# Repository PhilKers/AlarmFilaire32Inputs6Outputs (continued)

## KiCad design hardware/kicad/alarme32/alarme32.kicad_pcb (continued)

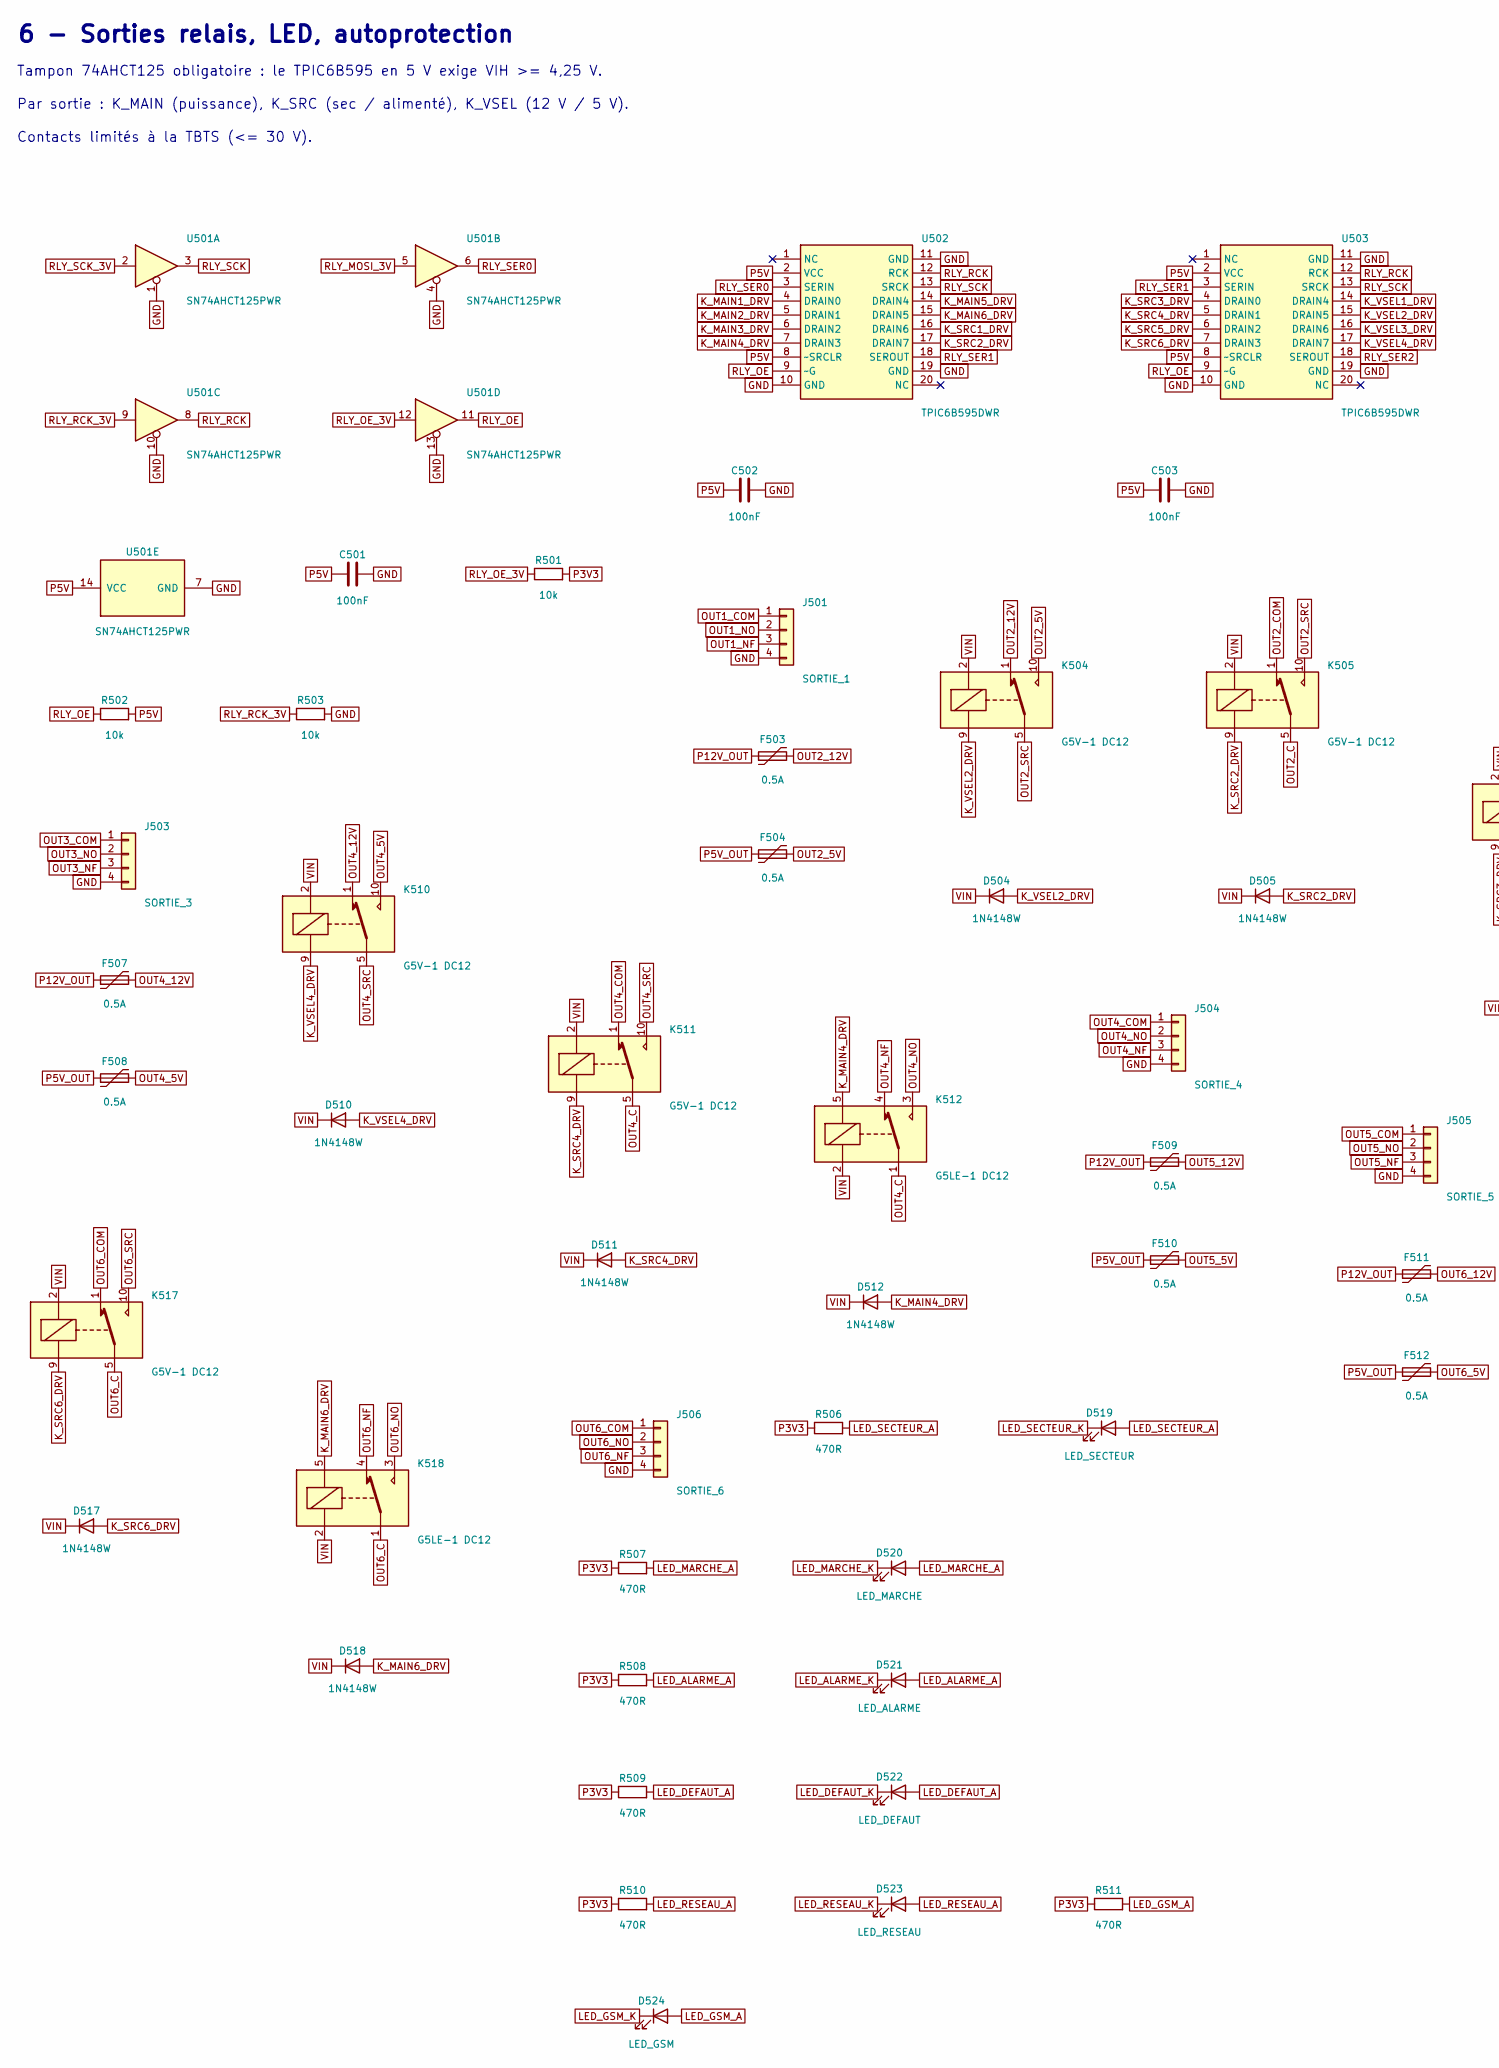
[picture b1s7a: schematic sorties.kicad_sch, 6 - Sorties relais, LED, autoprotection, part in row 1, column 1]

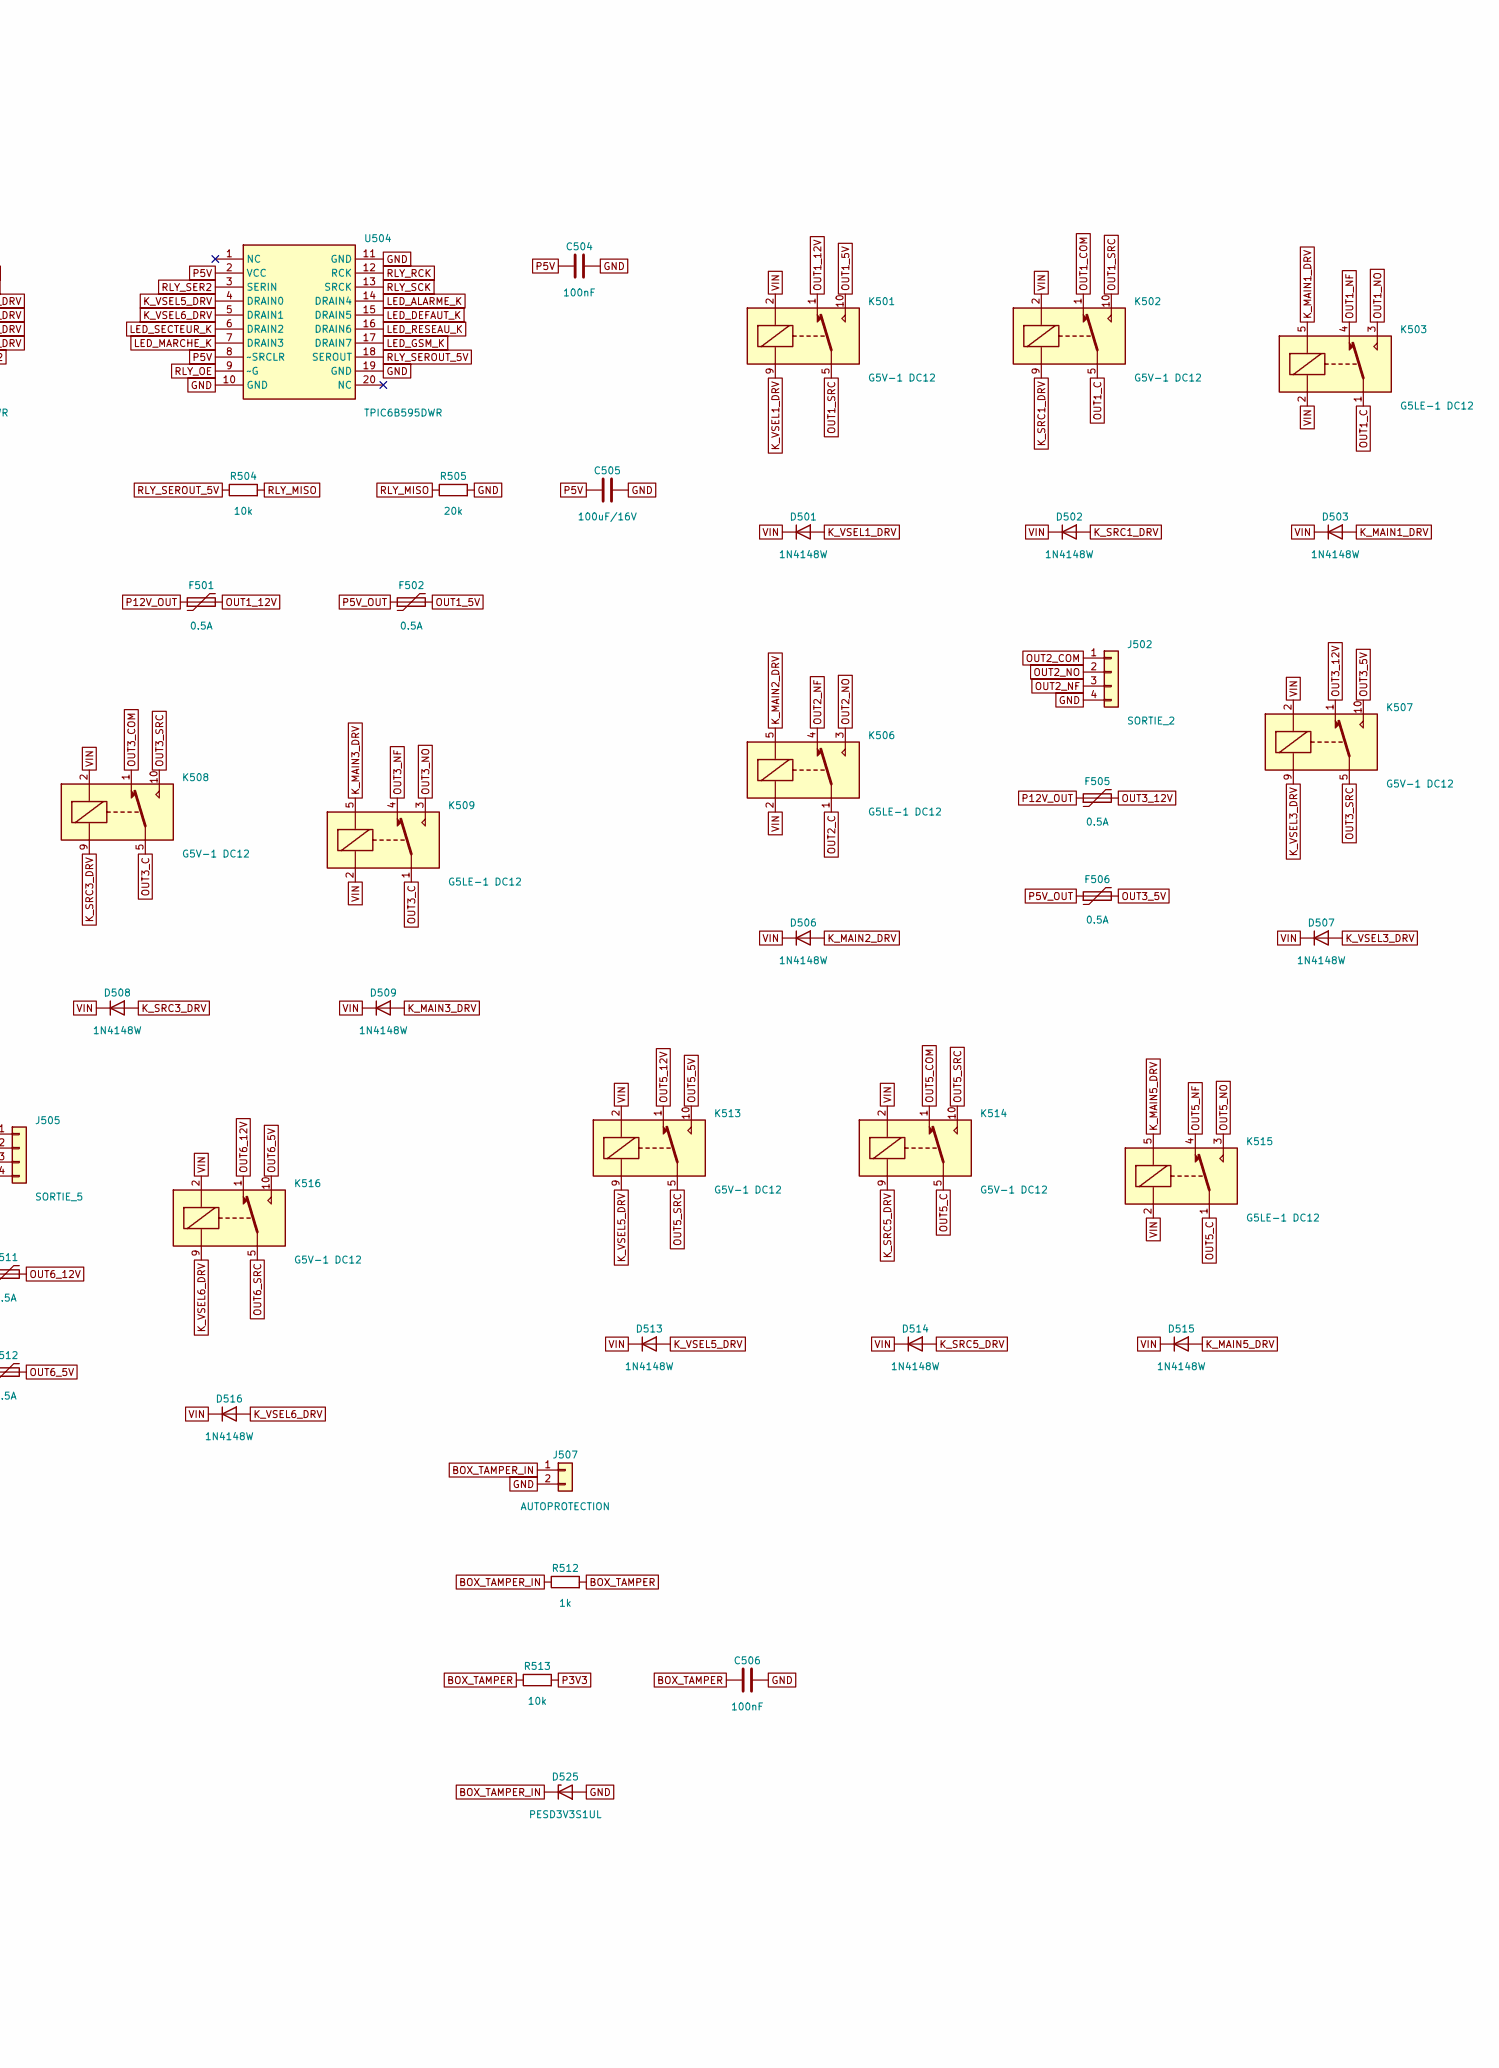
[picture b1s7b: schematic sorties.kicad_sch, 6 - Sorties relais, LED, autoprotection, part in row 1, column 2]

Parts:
C501, C502, C503, C504, C506: 100nF; C_0603_1608Metric
C505: 100uF/16V; C_1210_3225Metric
D501, D502, D503, D504, D505, D506, D507, D508, D509, D510, D511, D512, D513, D514, D515, D516, D517, D518: 1N4148W; D_SOD-123
D519: LED_SECTEUR; LED_D3.0mm
D520: LED_MARCHE; LED_D3.0mm
D521: LED_ALARME; LED_D3.0mm
D522: LED_DEFAUT; LED_D3.0mm
D523: LED_RESEAU; LED_D3.0mm
D524: LED_GSM; LED_D3.0mm
D525: PESD3V3S1UL; D_SOD-323
F501, F502, F503, F504, F505, F506, F507, F508, F509, F510, F511, F512: 0.5A; Fuse_1206_3216Metric
J501: SORTIE_1; TerminalBlock_Phoenix_MKDS-1,5-4-5.08_1x04_P5.08mm_Horizont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
J502: SORTIE_2; TerminalBlock_Phoenix_MKDS-1,5-4-5.08_1x04_P5.08mm_Horizont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
J503: SORTIE_3; TerminalBlock_Phoenix_MKDS-1,5-4-5.08_1x04_P5.08mm_Horizont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
J504: SORTIE_4; TerminalBlock_Phoenix_MKDS-1,5-4-5.08_1x04_P5.08mm_Horizont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
J505: SORTIE_5; TerminalBlock_Phoenix_MKDS-1,5-4-5.08_1x04_P5.08mm_Horizont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
J506: SORTIE_6; TerminalBlock_Phoenix_MKDS-1,5-4-5.08_1x04_P5.08mm_Horizont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
J507: AUTOPROTECTION; PinHeader_1x02_P2.54mm_Vertical
K501, K502, K504, K505, K507, K508, K510, K511, K513, K514, K516, K517: G5V-1 DC12; Relay_SPDT_Omron_G5V-1
K503, K506, K509, K512, K515, K518: G5LE-1 DC12; Relay_SPDT_Omron-G5LE-1
R501, R502, R503, R504, R513: 10k; R_0603_1608Metric
R505: 20k; R_0603_1608Metric
R506, R507, R508, R509, R510, R511: 470R; R_0603_1608Metric
R512: 1k; R_0603_1608Metric
U501: SN74AHCT125PWR; TSSOP-14_4.4x5mm_P0.65mm
U502, U503, U504: TPIC6B595DWR; SOIC-20W_7.5x12.8mm_P1.27mm

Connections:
BOX_TAMPER: C506.1, R512.2, R513.1; also elsewhere on the board
BOX_TAMPER_IN: D525.1 (K), J507.1, R512.1
GND: C501.2, C502.2, C503.2, C504.2, C505.2, C506.2, D525.2 (A), J501.4, J502.4, J503.4, J504.4, J505.4, J506.4, J507.2, R503.2, R505.2, U501.1, U501.4, U501.7 (GND), U501.10, U501.13, U502.10 (GND), U502.11 (GND), U502.19 (GND), U503.10 (GND), U503.11 (GND), U503.19 (GND), U504.10 (GND), U504.11 (GND), U504.19 (GND); also elsewhere on the board
K_MAIN1_DRV: D503.2 (A), K503.5, U502.4 (DRAIN0)
K_MAIN2_DRV: D506.2 (A), K506.5, U502.5 (DRAIN1)
K_MAIN3_DRV: D509.2 (A), K509.5, U502.6 (DRAIN2)
K_MAIN4_DRV: D512.2 (A), K512.5, U502.7 (DRAIN3)
K_MAIN5_DRV: D515.2 (A), K515.5, U502.14 (DRAIN4)
K_MAIN6_DRV: D518.2 (A), K518.5, U502.15 (DRAIN5)
K_SRC1_DRV: D502.2 (A), K502.9, U502.16 (DRAIN6)
K_SRC2_DRV: D505.2 (A), K505.9, U502.17 (DRAIN7)
K_SRC3_DRV: D508.2 (A), K508.9, U503.4 (DRAIN0)
K_SRC4_DRV: D511.2 (A), K511.9, U503.5 (DRAIN1)
K_SRC5_DRV: D514.2 (A), K514.9, U503.6 (DRAIN2)
K_SRC6_DRV: D517.2 (A), K517.9, U503.7 (DRAIN3)
K_VSEL1_DRV: D501.2 (A), K501.9, U503.14 (DRAIN4)
K_VSEL2_DRV: D504.2 (A), K504.9, U503.15 (DRAIN5)
K_VSEL3_DRV: D507.2 (A), K507.9, U503.16 (DRAIN6)
K_VSEL4_DRV: D510.2 (A), K510.9, U503.17 (DRAIN7)
K_VSEL5_DRV: D513.2 (A), K513.9, U504.4 (DRAIN0)
K_VSEL6_DRV: D516.2 (A), K516.9, U504.5 (DRAIN1)
LED_ALARME_A: D521.2 (A), R508.2
LED_ALARME_K: D521.1 (K), U504.14 (DRAIN4)
LED_DEFAUT_A: D522.2 (A), R509.2
LED_DEFAUT_K: D522.1 (K), U504.15 (DRAIN5)
LED_GSM_A: D524.2 (A), R511.2
LED_GSM_K: D524.1 (K), U504.17 (DRAIN7)
LED_MARCHE_A: D520.2 (A), R507.2
LED_MARCHE_K: D520.1 (K), U504.7 (DRAIN3)
LED_RESEAU_A: D523.2 (A), R510.2
LED_RESEAU_K: D523.1 (K), U504.16 (DRAIN6)
LED_SECTEUR_A: D519.2 (A), R506.2
LED_SECTEUR_K: D519.1 (K), U504.6 (DRAIN2)
OUT1_5V: F502.2, K501.10
OUT1_12V: F501.2, K501.1
OUT1_C: K502.5, K502.6, K503.1
OUT1_COM: J501.1, K502.1
OUT1_NF: J501.3, K503.4
OUT1_NO: J501.2, K503.3
OUT1_SRC: K501.5, K501.6, K502.10
OUT2_5V: F504.2, K504.10
OUT2_12V: F503.2, K504.1
OUT2_C: K505.5, K505.6, K506.1
OUT2_COM: J502.1, K505.1
OUT2_NF: J502.3, K506.4
OUT2_NO: J502.2, K506.3
OUT2_SRC: K504.5, K504.6, K505.10
OUT3_5V: F506.2, K507.10
OUT3_12V: F505.2, K507.1
OUT3_C: K508.5, K508.6, K509.1
OUT3_COM: J503.1, K508.1
OUT3_NF: J503.3, K509.4
OUT3_NO: J503.2, K509.3
OUT3_SRC: K507.5, K507.6, K508.10
OUT4_5V: F508.2, K510.10
OUT4_12V: F507.2, K510.1
OUT4_C: K511.5, K511.6, K512.1
OUT4_COM: J504.1, K511.1
OUT4_NF: J504.3, K512.4
OUT4_NO: J504.2, K512.3
OUT4_SRC: K510.5, K510.6, K511.10
OUT5_5V: F510.2, K513.10
OUT5_12V: F509.2, K513.1
OUT5_C: K514.5, K514.6, K515.1
OUT5_COM: J505.1, K514.1
OUT5_NF: J505.3, K515.4
OUT5_NO: J505.2, K515.3
OUT5_SRC: K513.5, K513.6, K514.10
OUT6_5V: F512.2, K516.10
OUT6_12V: F511.2, K516.1
OUT6_C: K517.5, K517.6, K518.1
OUT6_COM: J506.1, K517.1
OUT6_NF: J506.3, K518.4
OUT6_NO: J506.2, K518.3
OUT6_SRC: K516.5, K516.6, K517.10
P3V3: R501.2, R506.1, R507.1, R508.1, R509.1, R510.1, R511.1, R513.2; also elsewhere on the board
P5V: C501.1, C502.1, C503.1, C504.1, C505.1, R502.2, U501.14 (VCC), U502.2 (VCC), U502.8 (~SRCLR), U503.2 (VCC), U503.8 (~SRCLR), U504.2 (VCC), U504.8 (~SRCLR); also elsewhere on the board
P5V_OUT: F502.1, F504.1, F506.1, F508.1, F510.1, F512.1; also elsewhere on the board
P12V_OUT: F501.1, F503.1, F505.1, F507.1, F509.1, F511.1; also elsewhere on the board
RLY_MISO: R504.2, R505.1; also elsewhere on the board
RLY_MOSI_3V: U501.5; also elsewhere on the board
RLY_OE: R502.1, U501.11, U502.9 (~G), U503.9 (~G), U504.9 (~G)
RLY_OE_3V: R501.1, U501.12; also elsewhere on the board
RLY_RCK: U501.8, U502.12 (RCK), U503.12 (RCK), U504.12 (RCK)
RLY_RCK_3V: R503.1, U501.9; also elsewhere on the board
RLY_SCK: U501.3, U502.13 (SRCK), U503.13 (SRCK), U504.13 (SRCK)
RLY_SCK_3V: U501.2; also elsewhere on the board
RLY_SER0: U501.6, U502.3 (SERIN)
RLY_SER1: U502.18 (SEROUT), U503.3 (SERIN)
RLY_SER2: U503.18 (SEROUT), U504.3 (SERIN)
RLY_SEROUT_5V: R504.1, U504.18 (SEROUT)
VIN: D501.1 (K), D502.1 (K), D503.1 (K), D504.1 (K), D505.1 (K), D506.1 (K), D507.1 (K), D508.1 (K), D509.1 (K), D510.1 (K), D511.1 (K), D512.1 (K), D513.1 (K), D514.1 (K), D515.1 (K), D516.1 (K), D517.1 (K), D518.1 (K), K501.2, K502.2, K503.2, K504.2, K505.2, K506.2, K507.2, K508.2, K509.2, K510.2, K511.2, K512.2, K513.2, K514.2, K515.2, K516.2, K517.2, K518.2; also elsewhere on the board

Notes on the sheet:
6 - Sorties relais, LED, autoprotection
Tampon 74AHCT125 obligatoire : le TPIC6B595 en 5 V exige VIH >= 4,25 V.
Par sortie : K_MAIN (puissance), K_SRC (sec / alimenté), K_VSEL (12 V / 5 V).
Contacts limités à la TBTS (<= 30 V).

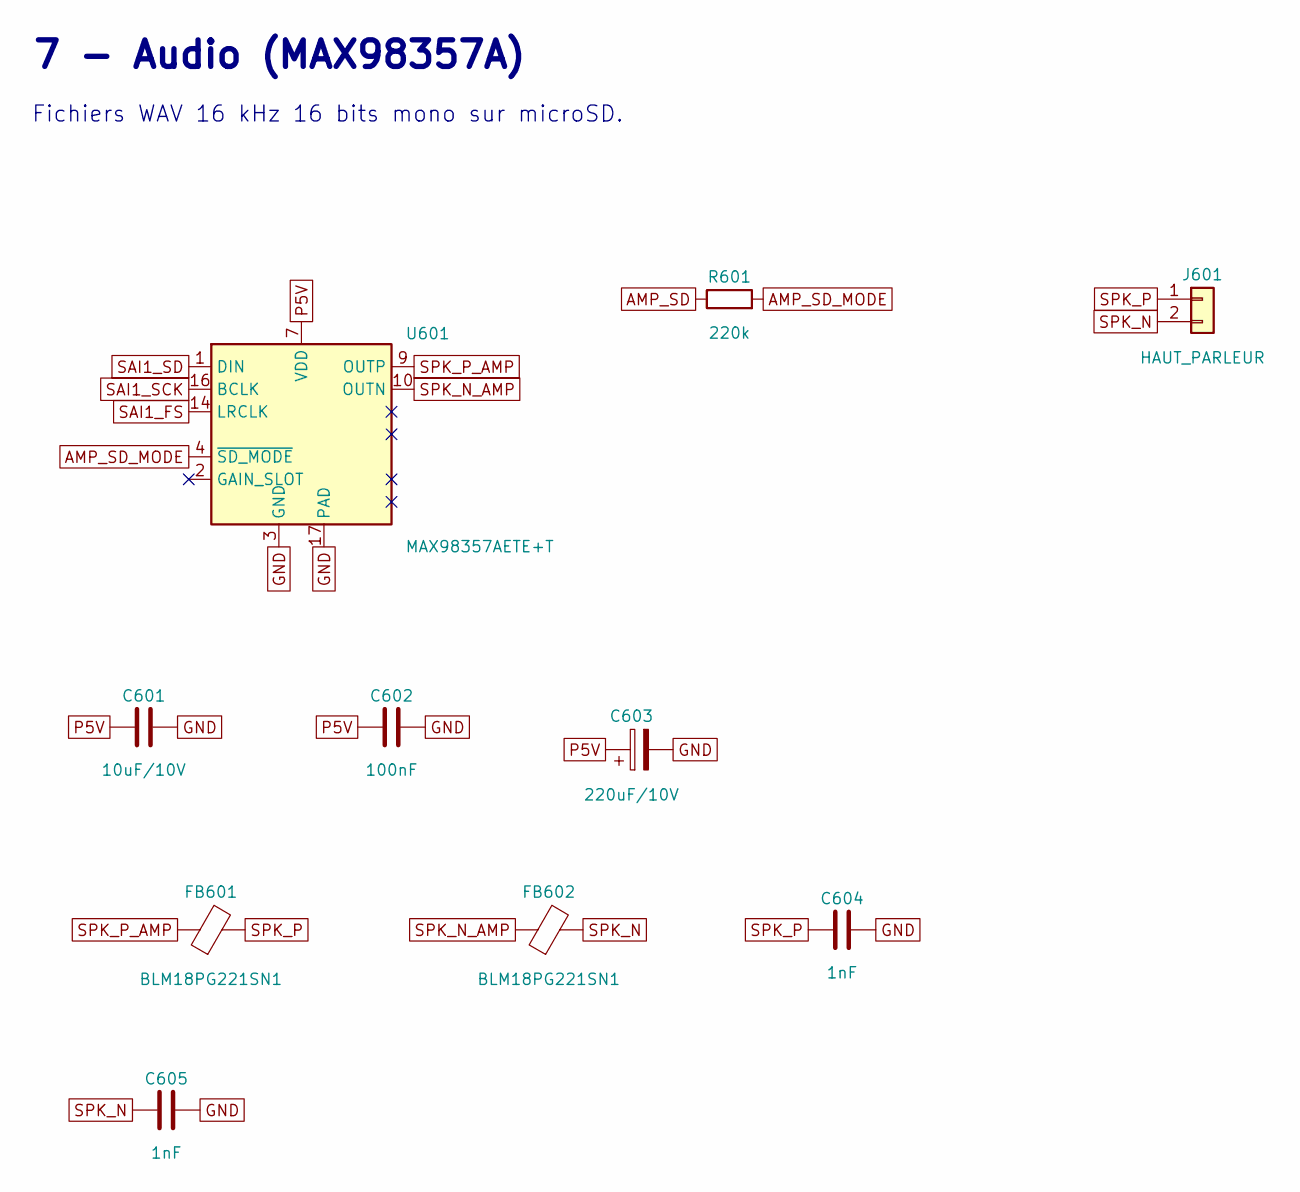
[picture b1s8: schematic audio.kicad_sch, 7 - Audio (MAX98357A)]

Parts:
C601: 10uF/10V; C_0805_2012Metric
C602: 100nF; C_0603_1608Metric
C603: 220uF/10V; CP_Elec_6.3x7.7
C604, C605: 1nF; C_0603_1608Metric
FB601, FB602: BLM18PG221SN1; R_0603_1608Metric
J601: HAUT_PARLEUR; TerminalBlock_Phoenix_MKDS-1,5-2-5.08_1x02_P5.08mm_Horizont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
R601: 220k; R_0603_1608Metric
U601: MAX98357AETE+T; TQFN-16-1EP_3x3mm_P0.5mm_EP1.23x1.23mm_ThermalVias

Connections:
AMP_SD: R601.1; also elsewhere on the board
AMP_SD_MODE: R601.2, U601.4 (~SD_MODE)
GND: C601.2, C602.2, C603.2, C604.2, C605.2, U601.3 (GND), U601.11 (GND), U601.15 (GND), U601.17 (PAD); also elsewhere on the board
P5V: C601.1, C602.1, C603.1, U601.7 (VDD), U601.8 (VDD); also elsewhere on the board
SAI1_FS: U601.14 (LRCLK); also elsewhere on the board
SAI1_SCK: U601.16 (BCLK); also elsewhere on the board
SAI1_SD: U601.1 (DIN); also elsewhere on the board
SPK_N: C605.1, FB602.2, J601.2
SPK_N_AMP: FB602.1, U601.10 (OUTN)
SPK_P: C604.1, FB601.2, J601.1
SPK_P_AMP: FB601.1, U601.9 (OUTP)

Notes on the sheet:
7 - Audio (MAX98357A)
Fichiers WAV 16 kHz 16 bits mono sur microSD.

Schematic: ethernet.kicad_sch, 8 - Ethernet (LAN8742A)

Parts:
C701, C702, C704, C709: 100nF; C_0603_1608Metric
C703: 10uF/10V; C_0805_2012Metric
C705: 1uF; C_0603_1608Metric
C706: 470pF; C_0603_1608Metric
C707, C708: 15pF; C_0603_1608Metric
FB701: BLM18PG221SN1; R_0603_1608Metric
J701: HR911105A; RJ45_Hanrun_HR911105A_Horizontal
R701: 12.1k; R_0603_1608Metric
R702, R703, R704, R705, R707: 10k; R_0603_1608Metric
R706: 1.5k; R_0603_1608Metric
R708, R709, R710, R711: 49.9R; R_0603_1608Metric
R712, R713: 330R; R_0603_1608Metric
U701: LAN8742A-CZ-TR; QFN-24-1EP_4x4mm_P0.5mm_EP2.6x2.6mm_ThermalVias
U702: TPD4E05U06DQAR; USON-10_2.5x1.0mm_P0.5mm
X701: 25MHz; Crystal_SMD_3225-4Pin_3.2x2.5mm

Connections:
ETH_CRS_DV: R704.1, U701.11 (CRS_DV/MODE2); also elsewhere on the board
ETH_LED_G_A: J701.9, R713.2
ETH_LED_Y_A: J701.12, R712.2
ETH_MDC: U701.13 (MDC); also elsewhere on the board
ETH_MDIO: R706.1, U701.12 (MDIO); also elsewhere on the board
ETH_REF_CLK: U701.14 (~INT/REFCLKO); also elsewhere on the board
ETH_RXD0: R702.1, U701.8 (RXD0/MODE0); also elsewhere on the board
ETH_RXD1: R703.1, U701.7 (RXD1/MODE1); also elsewhere on the board
ETH_RXN: J701.6 (RD-), R711.1, U701.22 (RXN), U702.5 (D2-)
ETH_RXP: J701.3 (RD+), R710.1, U701.23 (RXP), U702.4 (D2+)
ETH_TXD0: U701.17 (TXD0); also elsewhere on the board
ETH_TXD1: U701.18 (TXD1); also elsewhere on the board
ETH_TXN: J701.2 (TD-), R709.1, U701.20 (TXN), U702.2 (D1-)
ETH_TXP: J701.1 (TD+), R708.1, U701.21 (TXP), U702.1 (D1+)
ETH_TX_EN: U701.16 (TXEN); also elsewhere on the board
GND: C701.2, C702.2, C703.2, C704.2, C705.2, C706.2, C707.2, C708.2, C709.2, J701.8, J701.10, J701.11, J701.SH, R701.2, R705.2, U701.25 (VSS), U702.3 (GND), U702.8 (GND), X701.2 (G), X701.4 (G); also elsewhere on the board
P3V3: C704.1, FB701.1, R702.2, R703.2, R704.2, R706.2, R707.2, U701.9 (VDDIO); also elsewhere on the board
P3V3_PHY: C701.1, C702.1, C703.1, C709.1, FB701.2, J701.4 (TCT), J701.5 (RCT), R708.2, R709.2, R710.2, R711.2, U701.1 (VDD2A), U701.19 (VDD1A)
PHY_LED1: R712.1, U701.3 (LED1/REGOFF)
PHY_LED2: R713.1, U701.2 (LED2/~INTSEL)
PHY_RBIAS: R701.1, U701.24 (RBIAS)
PHY_RST: R707.1, U701.15 (~RST); also elsewhere on the board
PHY_RXER: R705.1, U701.10 (RXER/PHYAD0)
PHY_VDDCR: C705.1, C706.1, U701.6 (VDDCR)
PHY_XI: C707.1, U701.5 (XTAL1/CLKIN), X701.1
PHY_XO: C708.1, U701.4 (XTAL2), X701.3

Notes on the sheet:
8 - Ethernet (LAN8742A)
Straps : MODE = 111, PHYAD0 = 0, nINTSEL = 0 (sortie REFCLKO 50 MHz vers PA1).

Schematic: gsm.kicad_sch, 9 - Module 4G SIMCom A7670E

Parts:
C801: 470uF/6.3V; CP_Elec_8x10
C802: 100uF/6.3V; C_1210_3225Metric
C803: 10uF/10V; C_0805_2012Metric
C804, C806, C807, C811: 100nF; C_0603_1608Metric
C805, C808, C809, C810: 33pF; C_0603_1608Metric
C812, C813: NC; C_0603_1608Metric; not fitted
D801: SMF5.0A; D_SOD-123F
J801: MICRO_SIM; microSIM_JAE_SF53S006VCBR2000
J802: ANTENNE_LTE; U.FL_Hirose_U.FL-R-SMT-1_Vertical
Q801, Q802: MMBT3904; SOT-23
R801: 10k; R_0603_1608Metric
R802, R804: 4.7k; R_0603_1608Metric
R803, R805: 47k; R_0603_1608Metric
R806, R807: 100k; R_0603_1608Metric
R808, R809, R810: 22R; R_0603_1608Metric
R811: 0R; R_0603_1608Metric
TP801: MDM_USB_VBUS; TestPoint_Pad_D1.0mm
TP802: MDM_USB_DP; TestPoint_Pad_D1.0mm
TP803: MDM_USB_DM; TestPoint_Pad_D1.0mm
TP804: MDM_USB_BOOT; TestPoint_Pad_D1.0mm
TP805: MDM_LOG_TX; TestPoint_Pad_D1.0mm
TP806: MDM_LOG_RX; TestPoint_Pad_D1.0mm
TP807: MDM_NETLIGHT; TestPoint_Pad_D1.0mm
TP808: P3V3; TestPoint_Pad_D1.0mm
TP809: P5V; TestPoint_Pad_D1.0mm
TP810: VIN; TestPoint_Pad_D1.0mm
TP811: P3V8_GSM; TestPoint_Pad_D1.0mm
TP812: VZONE; TestPoint_Pad_D1.0mm
TP813: P12V_LCD; TestPoint_Pad_D1.0mm
TP814: GND; TestPoint_Pad_D1.0mm
U801: A7670E-LASE; SIMCom_A7670E_LGA-124_24x24mm
U802: TXS0108EPWR; TSSOP-20_4.4x6.5mm_P0.65mm
U803: ESDA6V1-5SC6; SOT-23-6

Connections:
ANT_MAIN: C812.1, R811.1, U801.60 (RF_ANT)
ANT_RF: C813.1, J802.1, R811.2
GND: C801.2, C802.2, C803.2, C804.2, C805.2, C806.2, C807.2, C808.2, C809.2, C810.2, C811.2, C812.2, C813.2, D801.2 (A), J801.5 (GND), J802.2, Q801.2 (E), Q802.2 (E), R803.2, R805.2, R806.2, R807.2, TP814.1, U801.2 (GND), U801.17 (GND), U801.18 (GND), U801.29 (GND), U801.39 (GND), U801.45 (GND), U801.46 (GND), U801.54 (GND), U801.58 (GND), U801.59 (GND), U801.61 (GND), U801.62 (GND), U801.63 (GND), U801.64 (GND), U801.65 (GND), U801.69 (GND), U801.70 (GND), U801.71 (GND), U801.72 (GND), U801.73 (GND), U801.74 (GND), U801.75 (GND), U801.76 (GND), U801.77 (GND), U801.78 (GND), U801.79 (GND), U801.80 (GND), U801.81 (GND), U801.82 (GND), U801.83 (GND), U801.84 (GND), U801.85 (GND), U801.86 (GND), U801.87 (GND), U801.88 (GND), U801.89 (GND), U801.91 (GND), U801.92 (GND), U801.94 (GND), U802.11 (GND), U803.2 (GND); also elsewhere on the board
MDM_1V8: C806.1, R801.1, U801.15 (VDD_1V8), U802.2 (VCCA)
MDM_CTS_18: U801.7 (CTS), U802.5 (A4)
MDM_DTR: U802.15 (B5); also elsewhere on the board
MDM_DTR_18: U801.3 (DTR), U802.6 (A5)
MDM_LOG_RX: TP806.1, U801.22 (UART_LOG_RX)
MDM_LOG_TX: TP805.1, U801.23 (UART_LOG_TX)
MDM_NETLIGHT: TP807.1, U801.52 (NETLIGHT)
MDM_OE: R801.2, U802.10 (OE)
MDM_PWRKEY: Q801.3 (C), U801.1 (PWRKEY)
MDM_PWRKEY_B: Q801.1 (B), R802.2, R803.1
MDM_PWRKEY_CTL: R802.1, R806.1; also elsewhere on the board
MDM_RESET: Q802.3 (C), U801.16 (RESET)
MDM_RESET_B: Q802.1 (B), R804.2, R805.1
MDM_RESET_CTL: R804.1, R807.1; also elsewhere on the board
MDM_RI: U802.14 (B6); also elsewhere on the board
MDM_RI_18: U801.4 (RI), U802.7 (A6)
MDM_RTS_18: U801.8 (RTS), U802.4 (A3)
MDM_RXD_18: U801.10 (RXD), U802.1 (A1)
MDM_STATUS: U802.13 (B7); also elsewhere on the board
MDM_STATUS_18: U801.66 (STATUS), U802.8 (A7)
MDM_TXD_18: U801.9 (TXD), U802.3 (A2)
MDM_USB_BOOT: TP804.1, U801.6 (USB_BOOT●)
MDM_USB_DM: TP803.1, U801.28 (USB_DM)
MDM_USB_DP: TP802.1, U801.27 (USB_DP)
MDM_USB_VBUS: TP801.1, U801.24 (VBUS)
P3V3: C807.1, TP808.1, U802.19 (VCCB); also elsewhere on the board
P3V8_GSM: C801.1, C802.1, C803.1, C804.1, C805.1, D801.1 (K), TP811.1, U801.55 (VBAT), U801.56 (VBAT), U801.57 (VBAT); also elsewhere on the board
P5V: TP809.1; also elsewhere on the board
P12V_LCD: TP813.1; also elsewhere on the board
SIM_CLK: C809.1, J801.3 (CLK), R809.2, U803.4 (IO3)
SIM_CLK_M: R809.1, U801.32 (USIM1_CLK)
SIM_DATA: C810.1, J801.7 (I/O), R810.2, U803.5 (IO4)
SIM_DATA_M: R810.1, U801.31 (USIM1_DATA)
SIM_RST: C808.1, J801.2 (RST), R808.2, U803.3 (IO2)
SIM_RST_M: R808.1, U801.33 (USIM1_RST)
SIM_VDD: C811.1, J801.1 (VCC), U801.30 (USIM1_VDD), U803.1 (IO1)
USART3_CTS: U802.16 (B4); also elsewhere on the board
USART3_RTS: U802.17 (B3); also elsewhere on the board
USART3_RX: U802.18 (B2); also elsewhere on the board
USART3_TX: U802.20 (B1); also elsewhere on the board
VIN: TP810.1; also elsewhere on the board
VZONE: TP812.1; also elsewhere on the board

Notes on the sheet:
9 - Module 4G SIMCom A7670E
Condensateur polymère 470 µF à moins de 10 mm des broches VBAT.
Piste d'antenne 50 Ω coplanaire, réseau en π (condensateurs non montés par défaut).

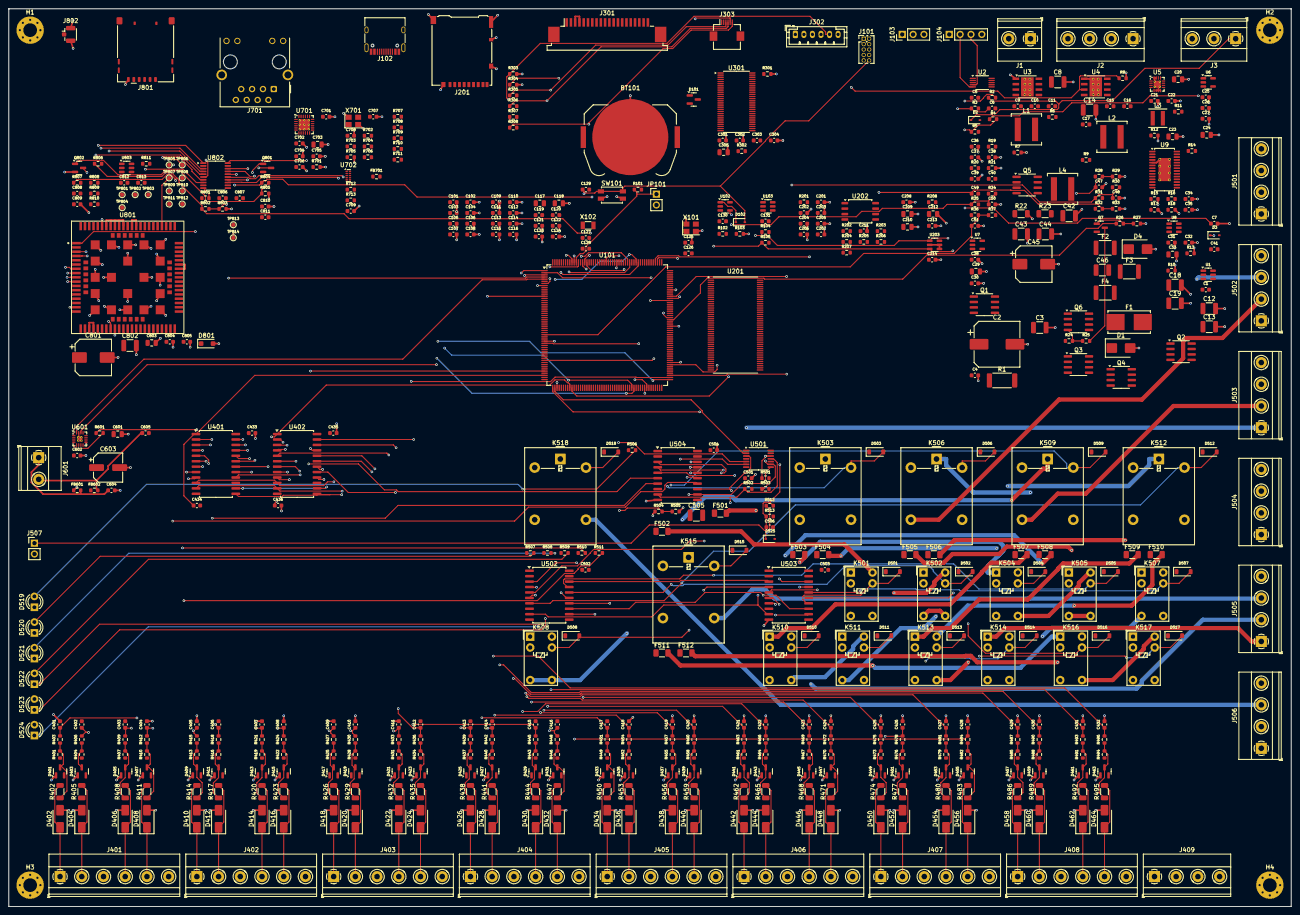
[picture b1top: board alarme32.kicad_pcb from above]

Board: 4 copper layers, 300.0 x 210.0 mm, 591 parts (0 on the bottom side), 466 nets.

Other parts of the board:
H1, H2, H3, H4: M3; MountingHole_3.2mm_M3_Pad_Via

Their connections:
GND: H1.1, H2.1, H3.1, H4.1; also elsewhere on the board

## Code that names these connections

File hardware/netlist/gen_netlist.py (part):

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    "VDD": "P3V3", "VSS": "GND", "VDDA": "P3V3A", "VREF+": "P3V3A", "VSSA": "GND",
    "VBAT": "VBAT_RTC", "VCAP": "VCAP", "VDD33_USB": "P3V3", "PDR_ON": "P3V3",
    "BOOT0": "BOOT0", "NRST": "NRST",
    "PH0": "OSC_IN", "PH1": "OSC_OUT", "PC14": "OSC32_IN", "PC15": "OSC32_OUT",
    # Débogage / USB / console
    "PA13": "SWDIO", "PA14": "SWCLK", "PB3": "SWO", "PA9": "DBG_TX", "PA10": "DBG_RX",
    "PA11": "USB_DM", "PA12": "USB_DP",
    # Tactile (I2C1)
    "PB8": "TP_SCL", "PB9": "TP_SDA", "PB7": "TP_INT", "PB4": "TP_RST",
    # Ethernet RMII
    "PA1": "ETH_REF_CLK", "PA2": "ETH_MDIO", "PC1": "ETH_MDC", "PA7": "ETH_CRS_DV",
    "PC4": "ETH_RXD0", "PC5": "ETH_RXD1", "PG11": "ETH_TX_EN", "PG13": "ETH_TXD0",
    "PG12": "ETH_TXD1", "PG10": "PHY_RST",
    # QSPI / SDMMC / I2C4
    "PB2": "QSPI_CLK", "PB6": "QSPI_NCS", "PF8": "QSPI_IO0", "PF9": "QSPI_IO1",
    "PF7": "QSPI_IO2", "PF6": "QSPI_IO3",
    "PC8": "SD_D0", "PC9": "SD_D1", "PC10": "SD_D2", "PC11": "SD_D3", "PC12": "SD_CK",
    "PD2": "SD_CMD", "PD11": "SD_DETECT", "PD12": "I2C4_SCL", "PD13": "I2C4_SDA",
    # Audio SAI1
    "PE4": "SAI1_FS", "PE5": "SAI1_SCK", "PE6": "SAI1_SD", "PE2": "AMP_SD",
    # Module 4G
    "PB10": "USART3_TX", "PB11": "USART3_RX", "PB13": "USART3_CTS", "PB14": "USART3_RTS",
    "PH6": "MDM_PWRKEY_CTL", "PH7": "MDM_RESET_CTL", "PI8": "MDM_STATUS", "PH4": "MDM_RI",
    "PI11": "MDM_DTR", "PE3": "MODEM_PWR_EN",
    # Zones
    "PA3": "MUXA_OUT", "PB0": "MUXB_OUT", "PB1": "ADC_VZONE",
    "PD4": "MUX_S0", "PD5": "MUX_S1", "PD6": "MUX_S2", "PD7": "MUX_S3",
    # Surveillance
    "PA4": "ADC_VIN", "PA0": "ADC_5V", "PC0": "ADC_AUX12", "PF10": "ADC_OUT12",
    "PA15": "AC_OK", "PB15": "BAT_LOW", "PG9": "BOX_TAMPER", "PG6": "AUX12_EN", "PG7": "WDI",
    # Relais (SPI1)
    "PA5": "RLY_SCK_3V", "PB5": "RLY_MOSI_3V", "PA6": "RLY_MISO", "PG14": "RLY_RCK_3V", "PG3": "RLY_OE_3V",
    # Écran
    "PA8": "BL_PWM", "PC13": "BL_EN", "PC7": "LCD_PWR_EN", "PC6": "LVDS_SHDN",
    "PI12": "LCD_HSYNC", "PI13": "LCD_VSYNC", "PI14": "LCD_CLK", "PK7": "LCD_DE",
    "PI15": "LCD_R0", "PJ0": "LCD_R1", "PJ1": "LCD_R2", "PJ2": "LCD_R3", "PJ3": "LCD_R4",
    "PJ4": "LCD_R5", "PJ5": "LCD_R6", "PJ6": "LCD_R7",
    "PJ7": "LCD_G0", "PJ8": "LCD_G1", "PJ9": "LCD_G2", "PJ10": "LCD_G3", "PJ11": "LCD_G4",
    "PK0": "LCD_G5", "PK1": "LCD_G6", "PK2": "LCD_G7",
    "PJ12": "LCD_B0", "PJ13": "LCD_B1", "PJ14": "LCD_B2", "PJ15": "LCD_B3",
    "PK3": "LCD_B4", "PK4": "LCD_B5", "PK5": "LCD_B6", "PK6": "LCD_B7",
    # SDRAM (FMC)
    "PG8": "SDCLK_MCU", "PH2": "SDR_CKE", "PH3": "SDR_CS", "PF11": "SDR_RAS",
    "PG15": "SDR_CAS", "PH5": "SDR_WE",
    "PE0": "SDR_DQM0", "PE1": "SDR_DQM1", "PI4": "SDR_DQM2", "PI5": "SDR_DQM3",
    "PG4": "SDR_BA0", "PG5": "SDR_BA1",
}
for i, p in enumerate(["PF0", "PF1", "PF2", "PF3", "PF4", "PF5", "PF12", "PF13", "PF14", "PF15", "PG0", "PG1"]):
    mcu[p] = f"SDR_A{i}"
dq = ["PD14", "PD15", "PD0", "PD1", "PE7", "PE8", "PE9", "PE10", "PE11", "PE12", "PE13", "PE14", "PE15",
      "PD8", "PD9", "PD10", "PH8", "PH9", "PH10", "PH11", "PH12", "PH13", "PH14", "PH15",
      "PI0", "PI1", "PI2", "PI3", "PI6", "PI7", "PI9", "PI10"]
for i, p in enumerate(dq):
    mcu[p] = f"SDR_DQ{i}"
U_MCU = B.ajoute("U", "STM32H743BIT6", "STM32H743BIT6", "LQFP208_28X28", "MCU Cortex-M7 480 MHz 2 Mo Flash",
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B.C("100nF", "NRST", "GND")
B.ajoute("SW", "SW_PUSH", "RESET", "SW_SMD_6X3_5", "Bouton RESET", ["NRST", "GND"])
B.R("10k", "BOOT0", "GND")
B.ajoute("JP", "JUMPER2", "BOOT0", "PINHEAD_1X2_2MM54", "Cavalier BOOT0 (DFU)", ["BOOT0", "P3V3"])
B.ajoute("U", "TPS3823-33DBV", "TPS3823-33DBVR", "SOT23_5", "Superviseur + chien de garde (1,6 s)",
         {"RESET": "WDG_RST", "GND": "GND", "WDI": "WDI", "VDD": "P3V3"}, base="TPS3823-33DBV", nc=["MR"])
B.decouple("P3V3")
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
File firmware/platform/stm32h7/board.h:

/**
 * @file board.h
 * @brief Affectation des broches de la carte centrale (STM32H743BIT6, LQFP208).
 *
 * Référence : docs/03-brochage-stm32.md. Les périphériques à fonction
 * alternée (FMC, LTDC, ETH, SDMMC, QUADSPI, SAI, USART, I2C, SPI) sont
 * initialisés par le code généré par STM32CubeMX (fichier .ioc) ; ce fichier
 * ne liste que les GPIO pilotés directement par l'application.
 */
#ifndef BOARD_H
#define BOARD_H
#include "stm32h7xx_hal.h"

/* --- Multiplexeurs analogiques des boucles (2 × CD74HC4067) ------------ */
#define MUX_S0_PORT         GPIOD
#define MUX_S0_PIN          GPIO_PIN_4
#define MUX_S1_PIN          GPIO_PIN_5
#define MUX_S2_PIN          GPIO_PIN_6
#define MUX_S3_PIN          GPIO_PIN_7      /* PD4..PD7 : même port, écriture BSRR */
#define MUX_ADDR_SHIFT      4u
/* MUX A (zones 1-16)  → PA3 = ADC1_INP15
 * MUX B (zones 17-32) → PB0 = ADC2_INP9
 * VZONE/2             → PB1 = ADC1_INP5
 * VIN/6               → PA4 = ADC1_INP18
 * +5V/2               → PA0 = ADC1_INP16
 * +12V AUX/6          → PC0 = ADC1_INP10
 * +12V OUT/6          → PF10 = ADC3_INP6                                 */

/* --- Chaîne relais (3 × TPIC6B595 sur SPI1) ----------------------------- */
#define RLY_RCK_PORT        GPIOG           /* Verrou (RCK)                 */
#define RLY_RCK_PIN         GPIO_PIN_14
#define RLY_OE_PORT         GPIOG           /* /G actif bas, pull-up 10k    */
#define RLY_OE_PIN          GPIO_PIN_3

/* --- Module 4G SIMCom A7670E (USART3 via TXS0108E 3V3↔1V8) ------------- */
#define MODEM_PWRKEY_PORT   GPIOH           /* via NPN : 1 = PWRKEY à 0     */
#define MODEM_PWRKEY_PIN    GPIO_PIN_6
#define MODEM_RESET_PORT    GPIOH           /* via NPN : 1 = RESET actif    */
#define MODEM_RESET_PIN     GPIO_PIN_7
#define MODEM_STATUS_PORT   GPIOI
#define MODEM_STATUS_PIN    GPIO_PIN_8
#define MODEM_RI_PORT       GPIOH
#define MODEM_RI_PIN        GPIO_PIN_4
#define MODEM_DTR_PORT      GPIOI
#define MODEM_DTR_PIN       GPIO_PIN_11
#define MODEM_PWR_EN_PORT   GPIOE           /* EN du régulateur 3,8 V       */
#define MODEM_PWR_EN_PIN    GPIO_PIN_3

/* --- Écran / dalle tactile ---------------------------------------------- */
#define LCD_BL_EN_PORT      GPIOC
#define LCD_BL_EN_PIN       GPIO_PIN_13
#define LCD_PWR_EN_PORT     GPIOC           /* Alimentation logique dalle   */
#define LCD_PWR_EN_PIN      GPIO_PIN_7
#define LVDS_SHDN_PORT      GPIOC           /* /SHTDN du SN75LVDS83B        */
#define LVDS_SHDN_PIN       GPIO_PIN_6
/* LCD_BL_PWM : PA8 = TIM1_CH1 (20 kHz) */
#define TOUCH_INT_PORT      GPIOB
#define TOUCH_INT_PIN       GPIO_PIN_7
#define TOUCH_RST_PORT      GPIOB
#define TOUCH_RST_PIN       GPIO_PIN_4

/* --- Audio --------------------------------------------------------------- */
#define AMP_SD_PORT         GPIOE           /* SD_MODE MAX98357A (0 = arrêt)*/
#define AMP_SD_PIN          GPIO_PIN_2

/* --- Divers ----------------------------------------------------------- */
#define SD_DETECT_PORT      GPIOD
#define SD_DETECT_PIN       GPIO_PIN_11
#define PHY_RST_PORT        GPIOG
#define PHY_RST_PIN         GPIO_PIN_10
/* PHY_INT non câblé : la broche nINT/REFCLKO du LAN8742A fournit le 50 MHz */
#define AC_OK_PORT          GPIOA           /* Contact AC OK du bloc PSC    */
#define AC_OK_PIN           GPIO_PIN_15
#define BAT_LOW_PORT        GPIOB           /* Contact BAT LOW du bloc PSC  */
#define BAT_LOW_PIN         GPIO_PIN_15
#define BOX_TAMPER_PORT     GPIOG           /* Contact d'autoprotection     */
#define BOX_TAMPER_PIN      GPIO_PIN_9
#define AUX12_EN_PORT       GPIOG           /* Coupure +12 V détecteurs     */
#define AUX12_EN_PIN        GPIO_PIN_6
#define WDI_PORT            GPIOG           /* Chien de garde TPS3823       */
#define WDI_PIN             GPIO_PIN_7

/* --- Ponts diviseurs (rapport de mesure) -------------------------------- */
#define DIV_VZONE           2u      /* 10k / 10k          */
#define DIV_5V              2u      /* 10k / 10k          */
#define DIV_12V             6u      /* 51k / 10k ≈ 6,1    */
#define DIV_12V_EXACT       6.1f

/* --- Adresses I2C (7 bits) ---------------------------------------------- */
#define I2C_ADDR_GT911      0x5Du
#define I2C_ADDR_INA226     0x40u
#define I2C_ADDR_EEPROM     0x50u   /* 24AA025E48 : adresse MAC unique     */

#endif /* BOARD_H */
